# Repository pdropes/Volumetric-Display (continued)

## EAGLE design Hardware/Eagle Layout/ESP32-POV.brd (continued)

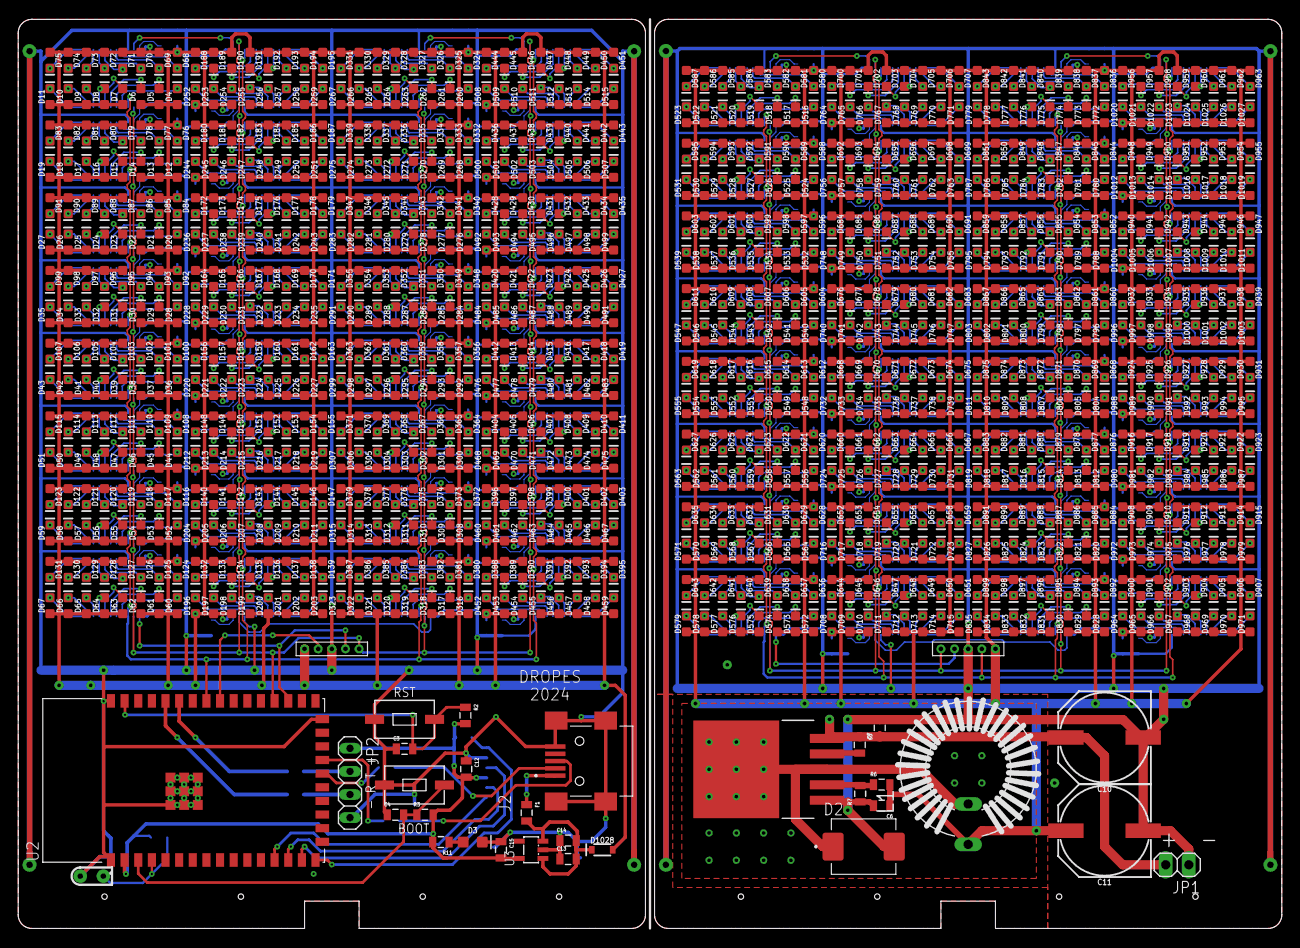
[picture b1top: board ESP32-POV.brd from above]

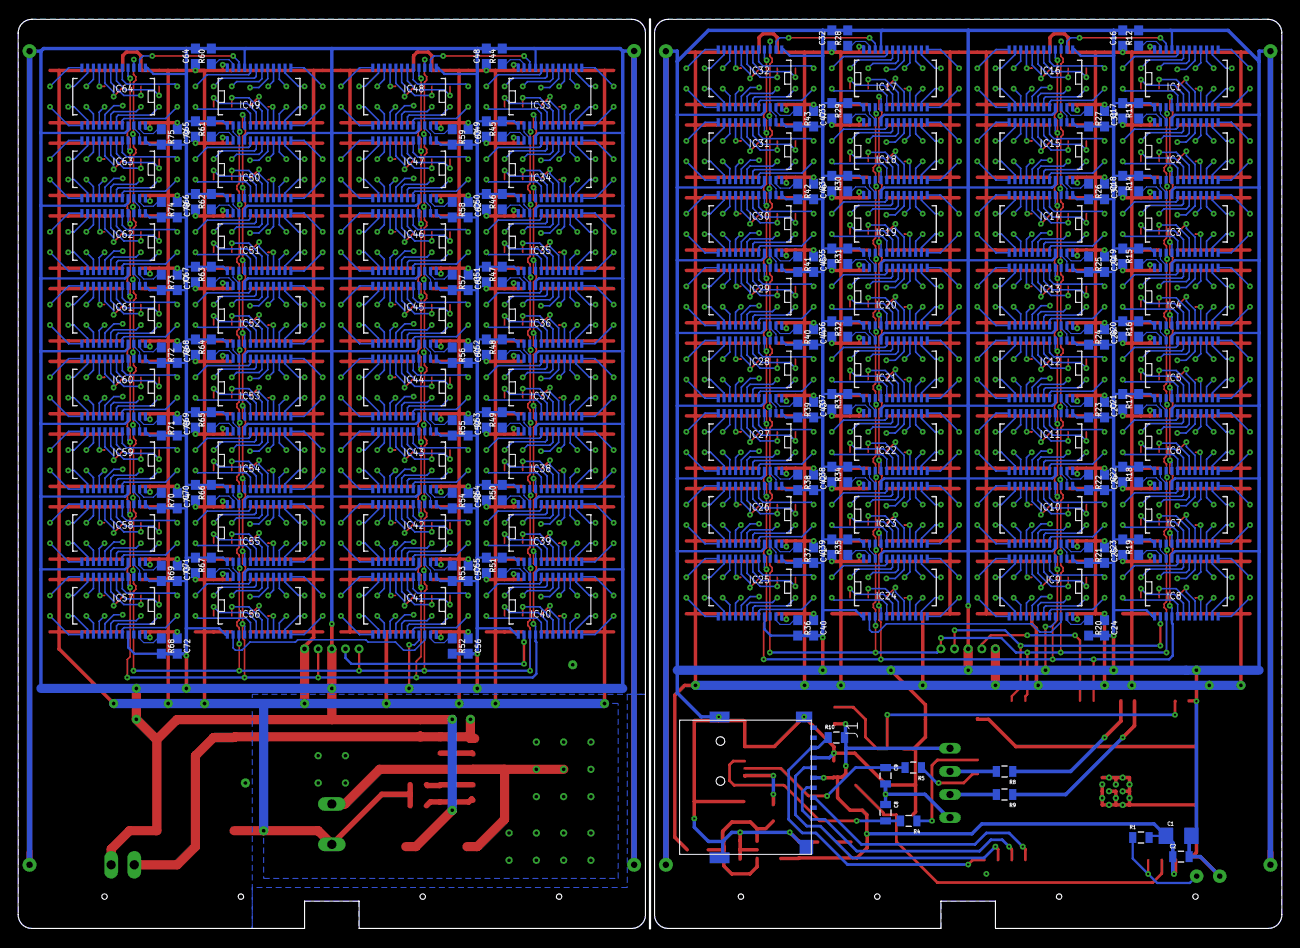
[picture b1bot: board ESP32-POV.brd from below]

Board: 2 copper layers, 139.0 x 100.0 mm, 1259 parts (203 on the bottom side), 1180 nets.

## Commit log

2024-09-21 Replace Photos directory
